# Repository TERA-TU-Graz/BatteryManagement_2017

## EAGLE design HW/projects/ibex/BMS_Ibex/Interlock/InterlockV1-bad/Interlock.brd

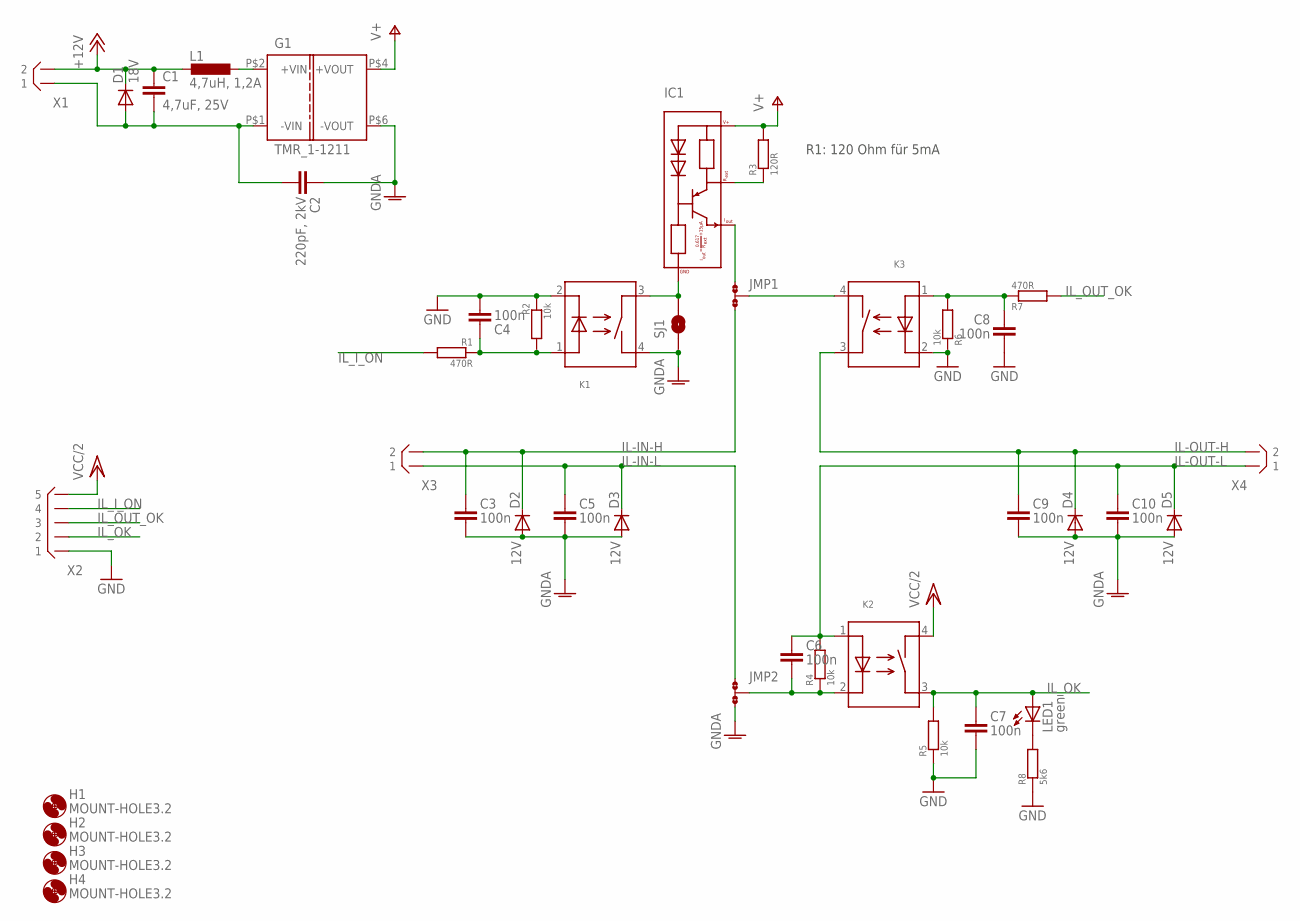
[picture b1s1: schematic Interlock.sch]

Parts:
C1: 4,7uF, 25V; C0805
C2: 220pF, 2kV; C1210_HV
C3, C4, C5, C6, C7, C8, C9, C10: 100n; C0805
D1: 18V; DO214AA
D2, D3, D4, D5: 12V; DO214AA
G1: TMR_1-1211; TMR_1-??1?
H1, H2, H3, H4: MOUNT-HOLE3.2; 3,2
IC1: PSSI2021SAY; SOT353
JMP1, JMP2: 0R-JUMPA; A0R-JMP
K1, K2, K3: ASSR-1218; SO-4
L1: 4,7uH, 1,2A; L3225M
LED1: green; CHIPLED_0805
R1, R7: 470R; R0805
R2, R4, R5, R6: 10k; R0805
R3: 120R; R0805
R8: 5k6; R0805
SJ1: SOLDERJUMPERNO; SJ_2S-NO
X1, X3, X4: B2B-XH
X2: B5B-XH

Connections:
+12V: C1.1, D1.C, L1.2, X1.P$2 (2)
GND: C4.1, C7.1, C8.1, K1.2 (I-), K3.2 (I-), R2.1, R5.1, R6.1, R8.1, X2.P$1 (1)
GNDA: C2.P$2 (2), C3.1, C5.1, C9.1, C10.1, D2.A, D3.A, D4.A, D5.A, G1.P$6 (-VOUT), JMP2.1, K1.4 (O1), SJ1.1
IL-IN-H: C3.2, D2.C, JMP1.3, X3.P$2 (2)
IL-IN-L: C5.2, D3.C, JMP2.3, X3.P$1 (1)
IL-OUT-H: C9.2, D4.C, K3.3 (O2), X4.P$2 (2)
IL-OUT-L: C6.2, C10.2, D5.C, K2.1 (I+), R4.2, X4.P$1 (1)
IL_I_ON: R1.2, X2.P$4 (4)
IL_OK: C7.2, K2.3 (O2), LED1.A, R5.2, X2.P$2 (2)
IL_OUT_OK: R7.2, X2.P$3 (3)
unnamed: IC1.4 (REXT), R3.1
unnamed: G1.P$2 (+VIN), L1.1
unnamed: C8.2, K3.1 (I+), R6.2, R7.1
unnamed: JMP1.2, K3.4 (O1)
unnamed: C1.2, C2.P$1 (1), D1.A, G1.P$1 (-VIN), X1.P$1 (1)
unnamed: IC1.2 (IOUT), JMP1.1
unnamed: C6.1, JMP2.2, K2.2 (I-), R4.1
unnamed: IC1.3 (GND), K1.3 (O2), SJ1.2
unnamed: C4.2, K1.1 (I+), R1.1, R2.2
unnamed: LED1.C, R8.2
V+: G1.P$4 (+VOUT), IC1.5 (VSS), R3.2
VCC/2: K2.4 (O1), X2.P$5 (5)

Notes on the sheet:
R1: 120 Ohm für 5mA

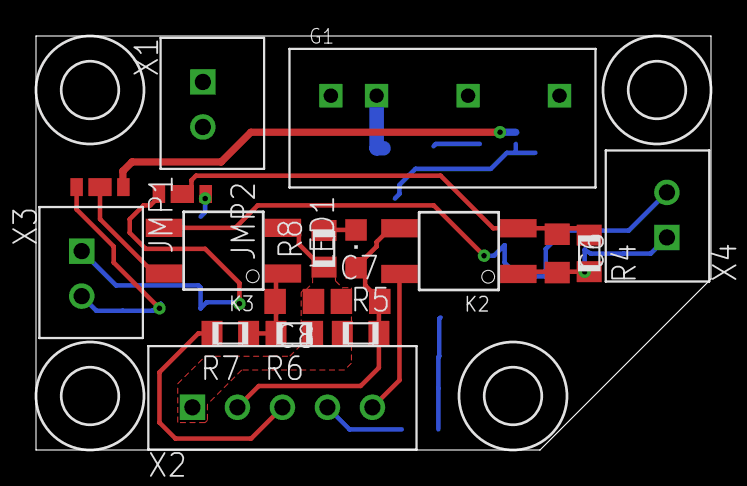
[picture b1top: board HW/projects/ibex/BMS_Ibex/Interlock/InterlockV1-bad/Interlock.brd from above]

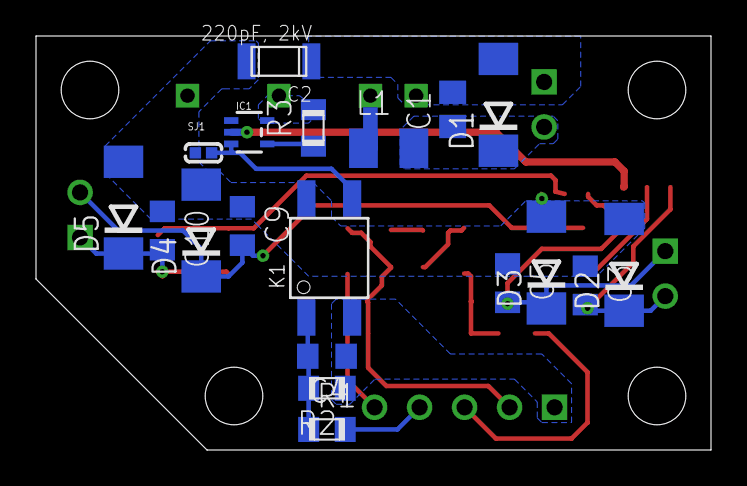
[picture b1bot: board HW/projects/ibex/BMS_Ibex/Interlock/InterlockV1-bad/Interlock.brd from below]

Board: 4 copper layers, 37.5 x 23.0 mm, 41 parts (19 on the bottom side), 22 nets.

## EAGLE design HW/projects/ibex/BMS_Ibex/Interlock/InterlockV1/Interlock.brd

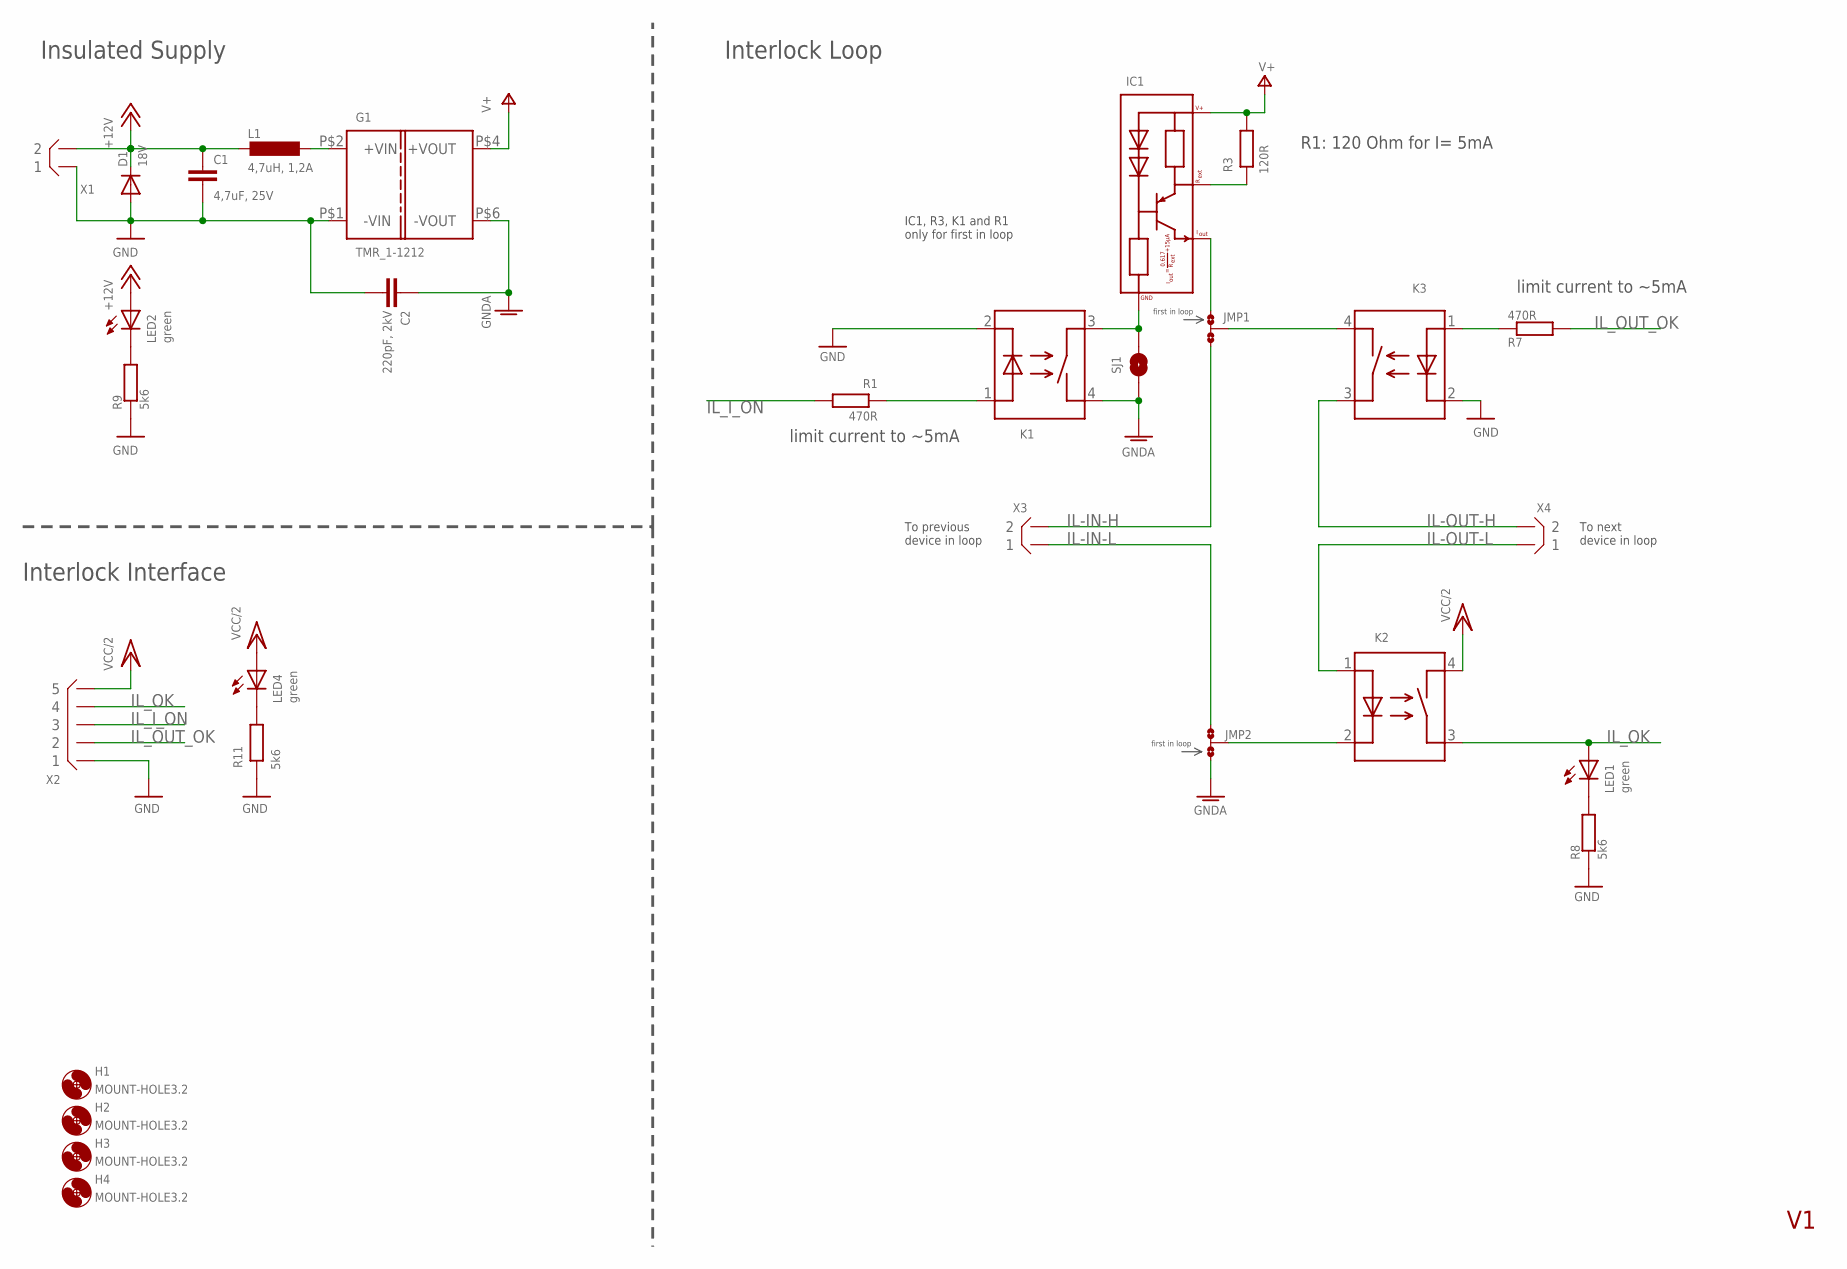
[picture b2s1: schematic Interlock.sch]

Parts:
C1: 4,7uF, 25V; C0805
C2: 220pF, 2kV; C1210_HV
D1: 18V; DO214AA
G1: TMR_1-1212; TMR_1-??1?
H1, H2, H3, H4: MOUNT-HOLE3.2; 3,2
IC1: PSSI2021SAY; SOT353
JMP1, JMP2: 0R-JUMPA; A0R-JMP
K1, K2, K3: ASSR-1218; SO-4
L1: 4,7uH, 1,2A; L3225M
LED1, LED2, LED4: green; CHIPLED_0805
R1, R7: 470R; R0805
R3: 120R; R0805
R8, R9, R11: 5k6; R0805
SJ1: SOLDERJUMPERNO; SJ_2S-NO
X1, X3, X4: B2B-XH
X2: B5B-XH

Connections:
+12V: C1.1, D1.C, L1.2, LED2.A, X1.P$2 (2)
GND: C1.2, C2.P$1 (1), D1.A, G1.P$1 (-VIN), K1.2 (I-), K3.2 (I-), R8.1, R9.1, R11.1, X1.P$1 (1), X2.P$1 (1)
GNDA: C2.P$2 (2), G1.P$6 (-VOUT), JMP2.1, K1.4 (O1), SJ1.1
IL-IN-H: JMP1.3, X3.P$2 (2)
IL-IN-L: JMP2.3, X3.P$1 (1)
IL-OUT-H: K3.3 (O2), X4.P$2 (2)
IL-OUT-L: K2.1 (I+), X4.P$1 (1)
IL_I_ON: R1.2, X2.P$3 (3)
IL_OK: K2.3 (O2), LED1.A, X2.P$4 (4)
IL_OUT_OK: R7.2, X2.P$2 (2)
unnamed: IC1.4 (REXT), R3.1
unnamed: G1.P$2 (+VIN), L1.1
unnamed: K3.1 (I+), R7.1
unnamed: JMP1.2, K3.4 (O1)
unnamed: IC1.2 (IOUT), JMP1.1
unnamed: JMP2.2, K2.2 (I-)
unnamed: IC1.3 (GND), K1.3 (O2), SJ1.2
unnamed: LED2.C, R9.2
unnamed: K1.1 (I+), R1.1
unnamed: LED4.C, R11.2
unnamed: LED1.C, R8.2
V+: G1.P$4 (+VOUT), IC1.5 (VSS), R3.2
VCC/2: K2.4 (O1), LED4.A, X2.P$5 (5)

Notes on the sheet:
R1: 120 Ohm for I= 5mA
limit current to ~5mA
Insulated Supply
Interlock Loop
Interlock Interface
IC1, R3, K1 and R1 only for first in loop
first in loop
To previous device in loop
To next device in loop

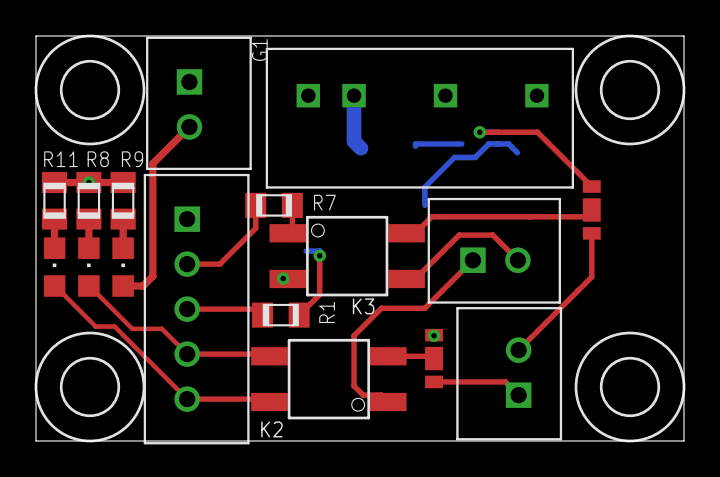
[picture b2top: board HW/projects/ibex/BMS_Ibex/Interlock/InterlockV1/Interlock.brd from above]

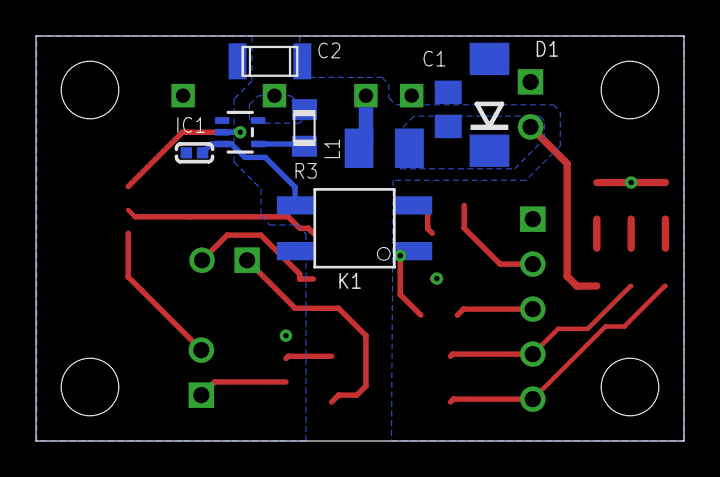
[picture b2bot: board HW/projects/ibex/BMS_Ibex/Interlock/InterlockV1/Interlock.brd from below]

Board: 4 copper layers, 36.0 x 22.5 mm, 29 parts (8 on the bottom side), 23 nets.

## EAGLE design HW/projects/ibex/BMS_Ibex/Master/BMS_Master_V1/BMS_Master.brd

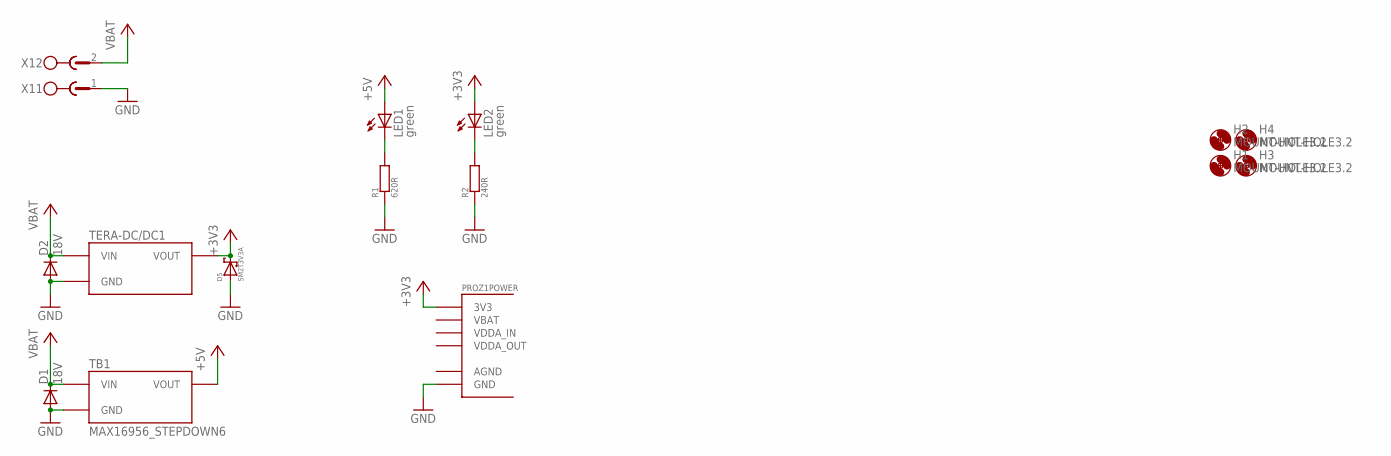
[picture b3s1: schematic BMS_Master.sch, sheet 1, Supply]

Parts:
D1, D2: 18V; DO214AA
D5: SM2T3V3A
H1, H2, H3, H4: MOUNT-HOLE3.2; 3,2
LED1, LED2: green; CHIP-LED0805
PROZ1: STM32F4_PROZESSORBOARDRPZ; STM32F4_PROZESSORBOARD
R1: 620R; R0805
R2: 240R; R0805
TB1: MAX16956_STEPDOWN6
TERA-DC/DC1: MAX5035_STEPDOWN3
X1: MSTBX2MSTBV2_GF; MSTBV2_GF

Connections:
+3V3: D5.P$2, LED2.A, PROZ1.45 (3V3), PROZ1.46 (3V3), TERA-DC/DC1.VOUT; also elsewhere on the board
+5V: LED1.A, TB1.VOUT; also elsewhere on the board
GND: D1.A, D2.A, D5.P$1, D5.P$11, PROZ1.47 (GND), PROZ1.48 (GND), R1.1, R2.1, TB1.GND, TB1.GND2 (GND), TERA-DC/DC1.GND@1 (GND), TERA-DC/DC1.GND@2 (GND), X1.1; also elsewhere on the board
unnamed: LED1.C, R1.2
unnamed: LED2.C, R2.2
VBAT: D1.C, D2.C, TB1.VIN, TERA-DC/DC1.VIN, X1.2; also elsewhere on the board

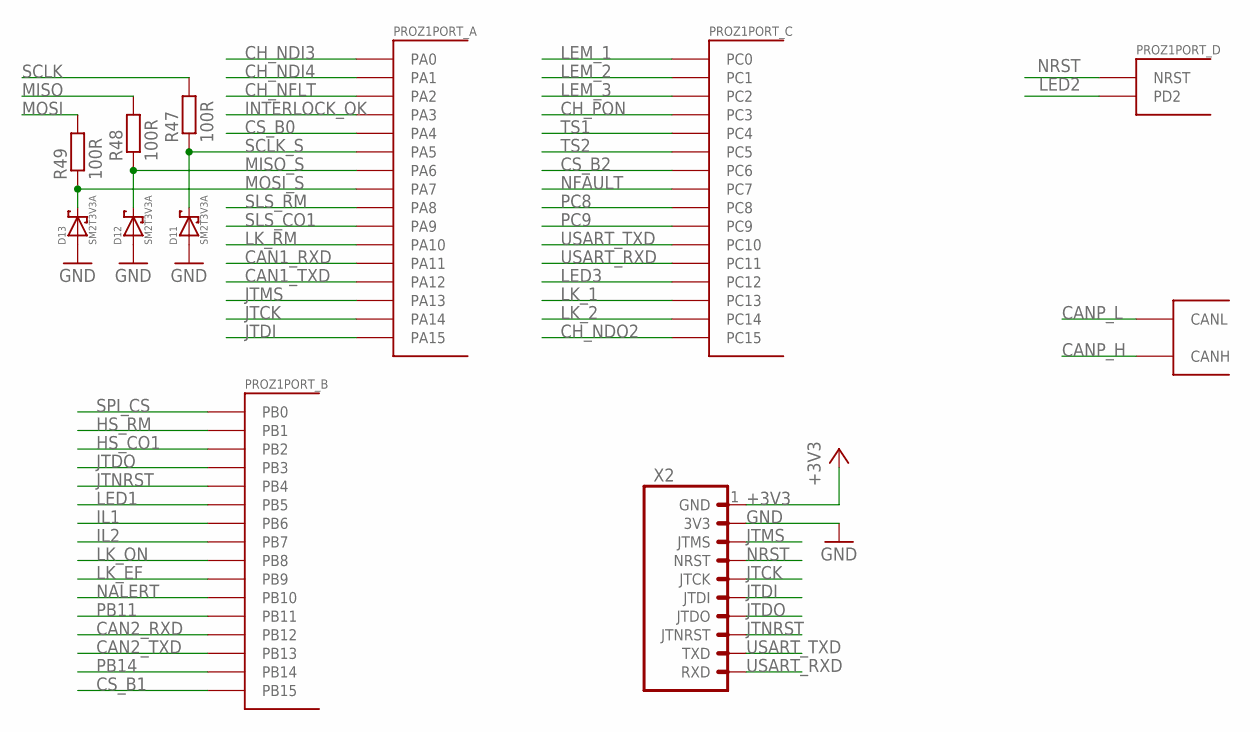
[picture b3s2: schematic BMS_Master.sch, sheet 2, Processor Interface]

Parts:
D11, D12, D13: SM2T3V3A
PROZ1: STM32F4_PROZESSORBOARDRPZ; STM32F4_PROZESSORBOARD
R47, R48, R49: 100R; R0805
X2: TERA-PROG-DEBUG-10GERADE; 90130-1110

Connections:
+3V3: X2.1 (GND); also elsewhere on the board
CAN1_RXD: PROZ1.26 (PA11); also elsewhere on the board
CAN1_TXD: PROZ1.24 (PA12); also elsewhere on the board
CAN2_RXD: PROZ1.50 (PB12); also elsewhere on the board
CAN2_TXD: PROZ1.49 (PB13); also elsewhere on the board
CANP_H: PROZ1.31 (CANH); also elsewhere on the board
CANP_L: PROZ1.32 (CANL); also elsewhere on the board
CH_NDI3: PROZ1.7 (PA0); also elsewhere on the board
CH_NDI4: PROZ1.5 (PA1); also elsewhere on the board
CH_NDO2: PROZ1.19 (PC15); also elsewhere on the board
CH_NFLT: PROZ1.3 (PA2); also elsewhere on the board
CH_PON: PROZ1.9 (PC3); also elsewhere on the board
CS_B0: PROZ1.43 (PA4); also elsewhere on the board
CS_B1: PROZ1.51 (PB15); also elsewhere on the board
CS_B2: PROZ1.52 (PC6); also elsewhere on the board
GND: D11.P$1, D11.P$11, D12.P$1, D12.P$11, D13.P$1, D13.P$11, X2.2 (3V3); also elsewhere on the board
HS_CO1: PROZ1.36 (PB2); also elsewhere on the board
HS_RM: PROZ1.37 (PB1); also elsewhere on the board
IL1: PROZ1.14 (PB6); also elsewhere on the board
IL2: PROZ1.12 (PB7); also elsewhere on the board
INTERLOCK_OK: PROZ1.44 (PA3); also elsewhere on the board
JTCK: PROZ1.18 (PA14), X2.5 (JTCK)
JTDI: PROZ1.16 (PA15), X2.6 (JTDI)
JTDO: PROZ1.20 (PB3), X2.7 (JTDO)
JTMS: PROZ1.59 (PA13), X2.3 (JTMS)
JTNRST: PROZ1.22 (PB4), X2.8 (JTNRST)
LED1: PROZ1.25 (PB5)
LED2: PROZ1.27 (PD2)
LED3: PROZ1.29 (PC12)
LEM_1: PROZ1.15 (PC0); also elsewhere on the board
LEM_2: PROZ1.13 (PC1); also elsewhere on the board
LEM_3: PROZ1.11 (PC2); also elsewhere on the board
LK_1: PROZ1.23 (PC13); also elsewhere on the board
LK_2: PROZ1.21 (PC14); also elsewhere on the board
LK_EF: PROZ1.8 (PB9); also elsewhere on the board
LK_ON: PROZ1.10 (PB8); also elsewhere on the board
LK_RM: PROZ1.58 (PA10); also elsewhere on the board
MISO: R48.2; also elsewhere on the board
MISO_S: D12.P$2, PROZ1.42 (PA6), R48.1
MOSI: R49.2; also elsewhere on the board
MOSI_S: D13.P$2, PROZ1.41 (PA7), R49.1
NALERT: PROZ1.35 (PB10); also elsewhere on the board
NFAULT: PROZ1.53 (PC7); also elsewhere on the board
NRST: PROZ1.17 (NRST), X2.4 (NRST)
PB11: PROZ1.34 (PB11)
PB14: PROZ1.33 (PB14)
PC8: PROZ1.54 (PC8)
PC9: PROZ1.55 (PC9)
SCLK: R47.2; also elsewhere on the board
SCLK_S: D11.P$2, PROZ1.60 (PA5), R47.1
SLS_CO1: PROZ1.57 (PA9); also elsewhere on the board
SLS_RM: PROZ1.56 (PA8); also elsewhere on the board
SPI_CS: PROZ1.38 (PB0); also elsewhere on the board
TS1: PROZ1.40 (PC4); also elsewhere on the board
TS2: PROZ1.39 (PC5); also elsewhere on the board
USART_RXD: PROZ1.30 (PC11), X2.10 (RXD)
USART_TXD: PROZ1.28 (PC10), X2.9 (TXD)

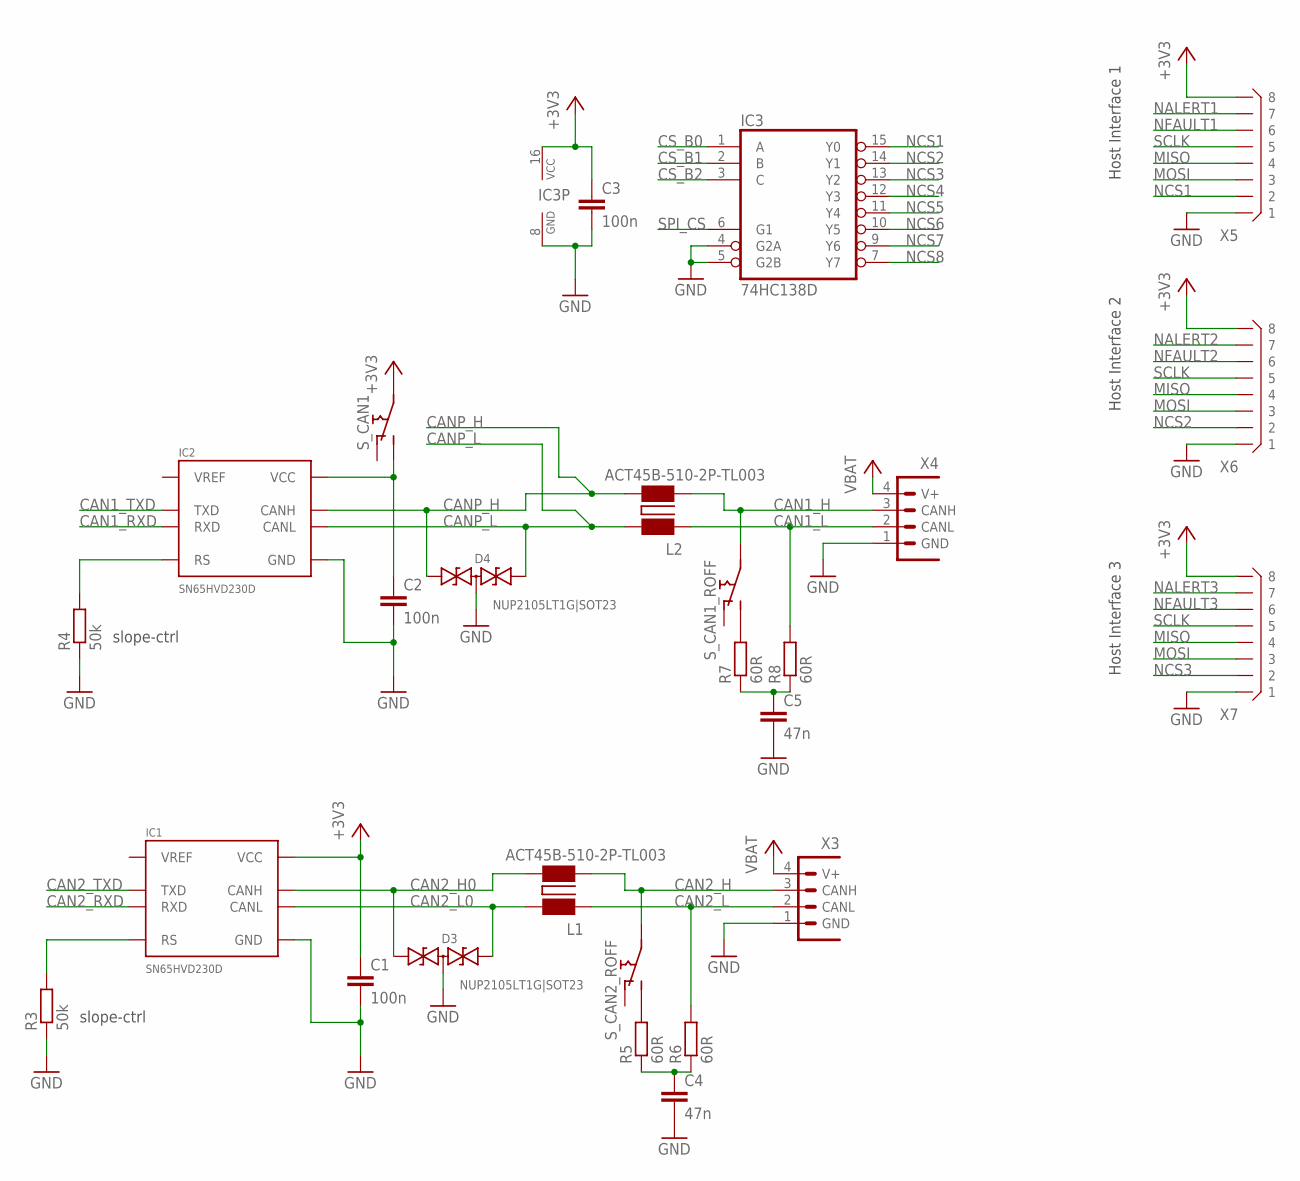
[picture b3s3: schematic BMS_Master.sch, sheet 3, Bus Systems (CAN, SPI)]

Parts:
C1, C2, C3: 100n; C0805
C4, C5: 47n; C0805
D3, D4: NUP2105LT1G|SOT23; SOT23
IC1, IC2: SN65HVD230D; SO08
IC3: 74HC138D; SO16
L1, L2: ACT45B-510-2P-TL003; ACT45B
R3, R4: 50k; R0805
R5, R6, R7, R8: 60R; R0805
S_CAN1, S_CAN1_ROFF, S_CAN2_ROFF: JUMPER_ORS; J_OR_S
X3, X4: CIOC_4-1-FV-A_CAN-BELEGUNG; CIOC_4-1-FV
X5, X6, X7: B8B-XH

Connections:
+3V3: C1.1, C3.1, IC1.3 (VCC), IC3.16 (VCC), S_CAN1.P$1, X5.P$8 (8), X6.P$8 (8), X7.P$8 (8); also elsewhere on the board
CAN1_H: L2.P$1 (1), S_CAN1_ROFF.P$1, X4.3 (CANH)
CAN1_L: L2.P$3 (3), R8.2, X4.2 (CANL)
CAN1_RXD: IC2.4 (RXD); also elsewhere on the board
CAN1_TXD: IC2.1 (TXD); also elsewhere on the board
CAN2_H: L1.P$1 (1), S_CAN2_ROFF.P$1, X3.3 (CANH)
CAN2_H0: D3.1, IC1.7 (CANH), L1.P$2 (2)
CAN2_L: L1.P$3 (3), R6.2, X3.2 (CANL)
CAN2_L0: D3.2, IC1.6 (CANL), L1.P$4 (4)
CAN2_RXD: IC1.4 (RXD); also elsewhere on the board
CAN2_TXD: IC1.1 (TXD); also elsewhere on the board
CANP_H: D4.1, IC2.7 (CANH), L2.P$2 (2); also elsewhere on the board
CANP_L: D4.2, IC2.6 (CANL), L2.P$4 (4); also elsewhere on the board
CS_B0: IC3.1 (A); also elsewhere on the board
CS_B1: IC3.2 (B); also elsewhere on the board
CS_B2: IC3.3 (C); also elsewhere on the board
GND: C1.2, C2.2, C3.2, C4.2, C5.2, D3.3, D4.3, IC1.2 (GND), IC2.2 (GND), IC3.4 (G2A), IC3.5 (G2B), IC3.8 (GND), R3.1, R4.1, X3.1 (GND), X4.1 (GND), X5.P$1 (1), X6.P$1 (1), X7.P$1 (1); also elsewhere on the board
MISO: X5.P$4 (4), X6.P$4 (4), X7.P$4 (4); also elsewhere on the board
MOSI: X5.P$3 (3), X6.P$3 (3), X7.P$3 (3); also elsewhere on the board
unnamed: C5.1, R7.1, R8.1
unnamed: C2.1, IC2.3 (VCC), S_CAN1.P$2
unnamed: IC2.8 (RS), R4.2
unnamed: C4.1, R5.1, R6.1
unnamed: R7.2, S_CAN1_ROFF.P$2
unnamed: IC1.8 (RS), R3.2
unnamed: R5.2, S_CAN2_ROFF.P$2
NALERT1: X5.P$7 (7); also elsewhere on the board
NALERT2: X6.P$7 (7); also elsewhere on the board
NALERT3: X7.P$7 (7); also elsewhere on the board
NCS1: IC3.15 (Y0), X5.P$2 (2)
NCS2: IC3.14 (Y1), X6.P$2 (2)
NCS3: IC3.13 (Y2), X7.P$2 (2)
NCS4: IC3.12 (Y3); also elsewhere on the board
NCS5: IC3.11 (Y4); also elsewhere on the board
NCS6: IC3.10 (Y5)
NCS7: IC3.9 (Y6)
NCS8: IC3.7 (Y7)
NFAULT1: X5.P$6 (6); also elsewhere on the board
NFAULT2: X6.P$6 (6); also elsewhere on the board
NFAULT3: X7.P$6 (6); also elsewhere on the board
SCLK: X5.P$5 (5), X6.P$5 (5), X7.P$5 (5); also elsewhere on the board
SPI_CS: IC3.6 (G1); also elsewhere on the board
VBAT: X3.4 (V+), X4.4 (V+); also elsewhere on the board

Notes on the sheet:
slope-ctrl
Host Interface 1
Host Interface 2
Host Interface 3

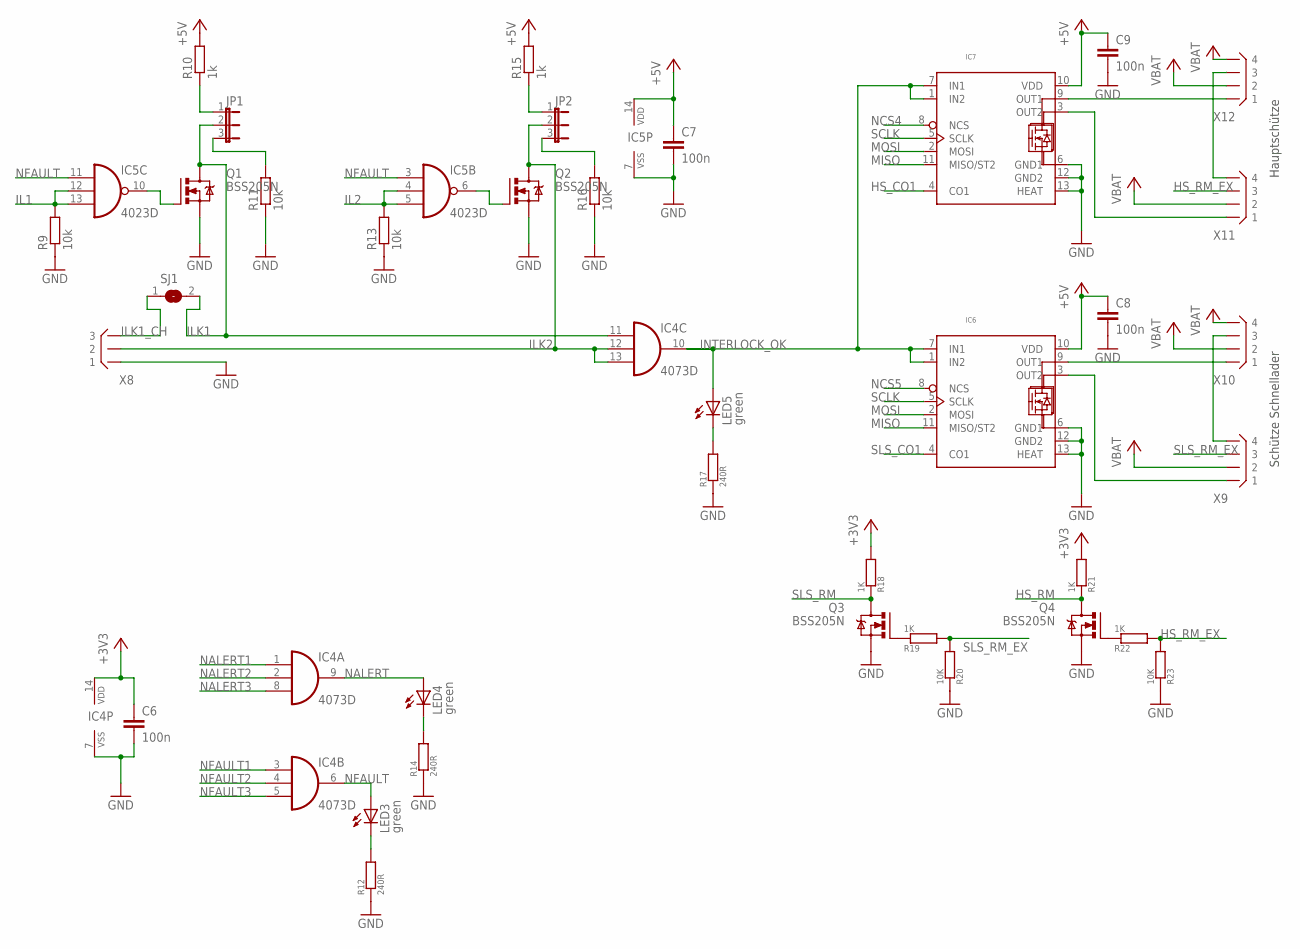
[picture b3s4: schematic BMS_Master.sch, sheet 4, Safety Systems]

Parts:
C6, C7, C8, C9: 100n; C0805
IC4: 4073D; SO14
IC5: 4023D; SO14
IC6, IC7: TLE8102SGN; INF-PG-DSO-12-11_N_1PRIMARY
JP1, JP2: JP2E; JP2
LED3, LED4, LED5: green; CHIPLED_0805
Q1, Q2, Q3, Q4: BSS205N; SOT23
R9, R11, R13, R16: 10k; R0805
R10, R15: 1k; R0805
R12, R14, R17: 240R; R0805
R18, R19, R21, R22: 1K; R0805
R20, R23: 10K; R0805
SJ1: SJ
X8: B3B-XH
X9, X10, X11, X12: B4B-XH

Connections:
+3V3: C6.1, IC4.14 (VDD), R18.2, R21.2; also elsewhere on the board
+5V: C7.1, C8.1, C9.1, IC5.14 (VDD), IC6.10 (VDD), IC7.10 (VDD), R10.2, R15.2; also elsewhere on the board
GND: C6.2, C7.2, C8.2, C9.2, IC4.7 (VSS), IC5.7 (VSS), IC6.6 (GND1), IC6.12 (GND2), IC6.13 (HEAT), IC7.6 (GND1), IC7.12 (GND2), IC7.13 (HEAT), Q1.2 (S), Q2.2 (S), Q3.2 (S), Q4.2 (S), R9.1, R11.1, R12.1, R13.1, R14.1, R16.1, R17.1, R20.1, R23.1, X8.P$1 (1); also elsewhere on the board
HS_CO1: IC7.4 (CO1); also elsewhere on the board
HS_RM: Q4.3 (D), R21.1; also elsewhere on the board
HS_RM_EX: R22.2, R23.2, X11.P$3 (3)
IL1: IC5.12 (I1), IC5.13 (I2), R9.2; also elsewhere on the board
IL2: IC5.4 (I1), IC5.5 (I2), R13.2; also elsewhere on the board
ILK1: IC4.11 (I0), JP1.2, Q1.3 (D), SJ1.2; also elsewhere on the board
ILK1_CH: SJ1.1, X8.P$3 (3); also elsewhere on the board
ILK2: IC4.12 (I1), IC4.13 (I2), JP2.2, Q2.3 (D), X8.P$2 (2)
INTERLOCK_OK: IC4.10 (O), IC6.1 (IN2), IC6.7 (IN1), IC7.1 (IN2), IC7.7 (IN1), LED5.A; also elsewhere on the board
MISO: IC6.11 (MISO/ST2), IC7.11 (MISO/ST2); also elsewhere on the board
MOSI: IC6.2 (MOSI), IC7.2 (MOSI); also elsewhere on the board
unnamed: X9.P$4 (4), X10.P$3 (3)
unnamed: IC7.3 (OUT2), X11.P$1 (1)
unnamed: IC6.9 (OUT1), X10.P$1 (1)
unnamed: X11.P$4 (4), X12.P$3 (3)
unnamed: IC6.3 (OUT2), X9.P$1 (1)
unnamed: IC7.9 (OUT1), X12.P$1 (1)
unnamed: JP1.1, R10.1
unnamed: IC5.10 (O), Q1.1 (G)
unnamed: IC5.6 (O), Q2.1 (G)
unnamed: JP2.1, R15.1
unnamed: JP2.3, R16.2
unnamed: JP1.3, R11.2
unnamed: LED5.C, R17.2
unnamed: LED4.C, R14.2
unnamed: LED3.C, R12.2
unnamed: Q3.1 (G), R19.1
unnamed: Q4.1 (G), R22.1
NALERT: IC4.9 (O), LED4.A; also elsewhere on the board
NALERT1: IC4.1 (I0); also elsewhere on the board
NALERT2: IC4.2 (I1); also elsewhere on the board
NALERT3: IC4.8 (I2); also elsewhere on the board
NCS4: IC7.8 (NCS); also elsewhere on the board
NCS5: IC6.8 (NCS); also elsewhere on the board
NFAULT: IC4.6 (O), IC5.3 (I0), IC5.11 (I0), LED3.A; also elsewhere on the board
NFAULT1: IC4.3 (I0); also elsewhere on the board
NFAULT2: IC4.4 (I1); also elsewhere on the board
NFAULT3: IC4.5 (I2); also elsewhere on the board
SCLK: IC6.5 (SCLK), IC7.5 (SCLK); also elsewhere on the board
SLS_CO1: IC6.4 (CO1); also elsewhere on the board
SLS_RM: Q3.3 (D), R18.1; also elsewhere on the board
SLS_RM_EX: R19.2, R20.2, X9.P$3 (3)
VBAT: X9.P$2 (2), X10.P$2 (2), X10.P$4 (4), X11.P$2 (2), X12.P$2 (2), X12.P$4 (4); also elsewhere on the board

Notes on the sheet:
Hauptschütze
Schütze Schnellader

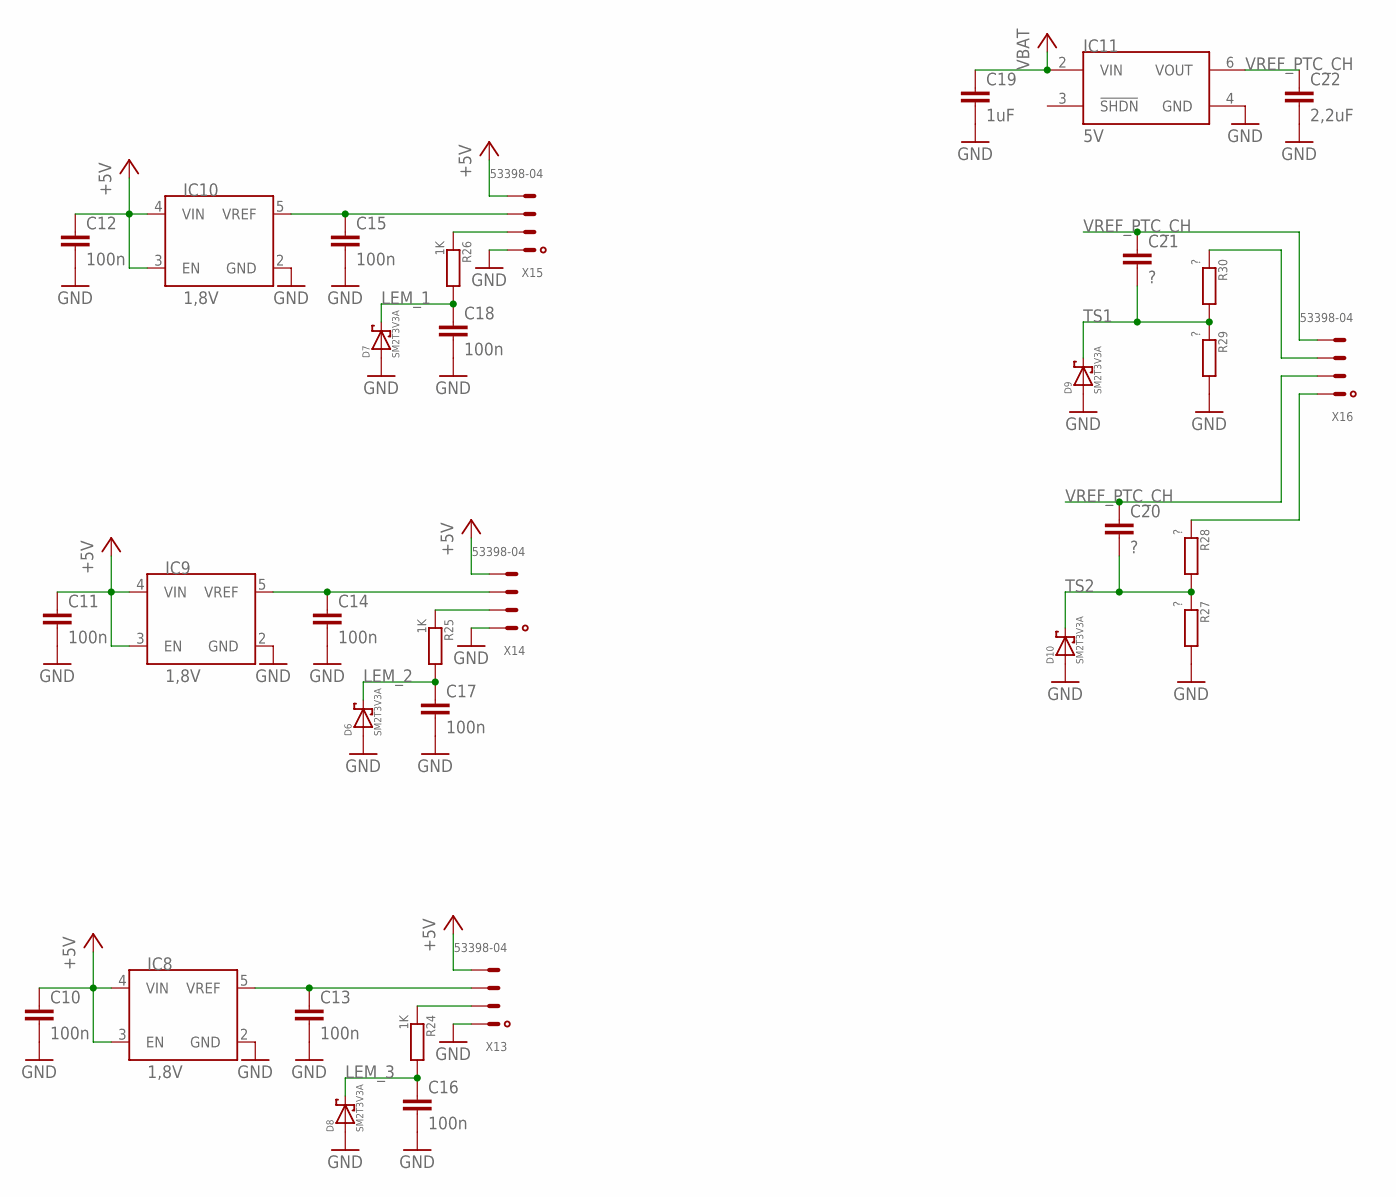
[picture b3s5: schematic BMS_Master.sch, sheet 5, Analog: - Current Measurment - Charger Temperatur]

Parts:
C10, C11, C12, C13, C14, C15, C16, C17, C18: 100n; C0805
C19: 1uF; C0805
C20, C21: ?; C0805
C22: 2,2uF; C0805
D6, D7, D8, D9, D10: SM2T3V3A
IC8, IC9, IC10: 1,8V; SOT23-5L
IC11: 5V; SO08
R24, R25, R26: 1K; R0805
R27, R28, R29, R30: ?; R0805
X13, X14, X15, X16: 53398-04

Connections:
+5V: C10.1, C11.1, C12.1, IC8.3 (EN), IC8.4 (VIN), IC9.3 (EN), IC9.4 (VIN), IC10.3 (EN), IC10.4 (VIN), X13.4, X14.4, X15.4; also elsewhere on the board
GND: C10.2, C11.2, C12.2, C13.2, C14.2, C15.2, C16.2, C17.2, C18.2, C19.2, C22.2, D6.P$1, D6.P$11, D7.P$1, D7.P$11, D8.P$1, D8.P$11, D9.P$1, D9.P$11, D10.P$1, D10.P$11, IC8.2 (GND), IC9.2 (GND), IC10.2 (GND), IC11.4 (GND), R27.2, R29.2, X13.1, X14.1, X15.1; also elsewhere on the board
LEM_1: C18.1, D7.P$2, R26.2; also elsewhere on the board
LEM_2: C17.1, D6.P$2, R25.2; also elsewhere on the board
LEM_3: C16.1, D8.P$2, R24.2; also elsewhere on the board
unnamed: C13.1, IC8.5 (VREF), X13.3
unnamed: R26.1, X15.2
unnamed: C14.1, IC9.5 (VREF), X14.3
unnamed: R30.1, X16.3
unnamed: R25.1, X14.2
unnamed: C15.1, IC10.5 (VREF), X15.3
unnamed: R24.1, X13.2
unnamed: R28.1, X16.1
TS1: C21.2, D9.P$2, R29.1, R30.2; also elsewhere on the board
TS2: C20.2, D10.P$2, R27.1, R28.2; also elsewhere on the board
VBAT: C19.1, IC11.2 (VIN); also elsewhere on the board
VREF_PTC_CH: C20.1, C21.1, C22.1, IC11.6 (VOUT), X16.2, X16.4

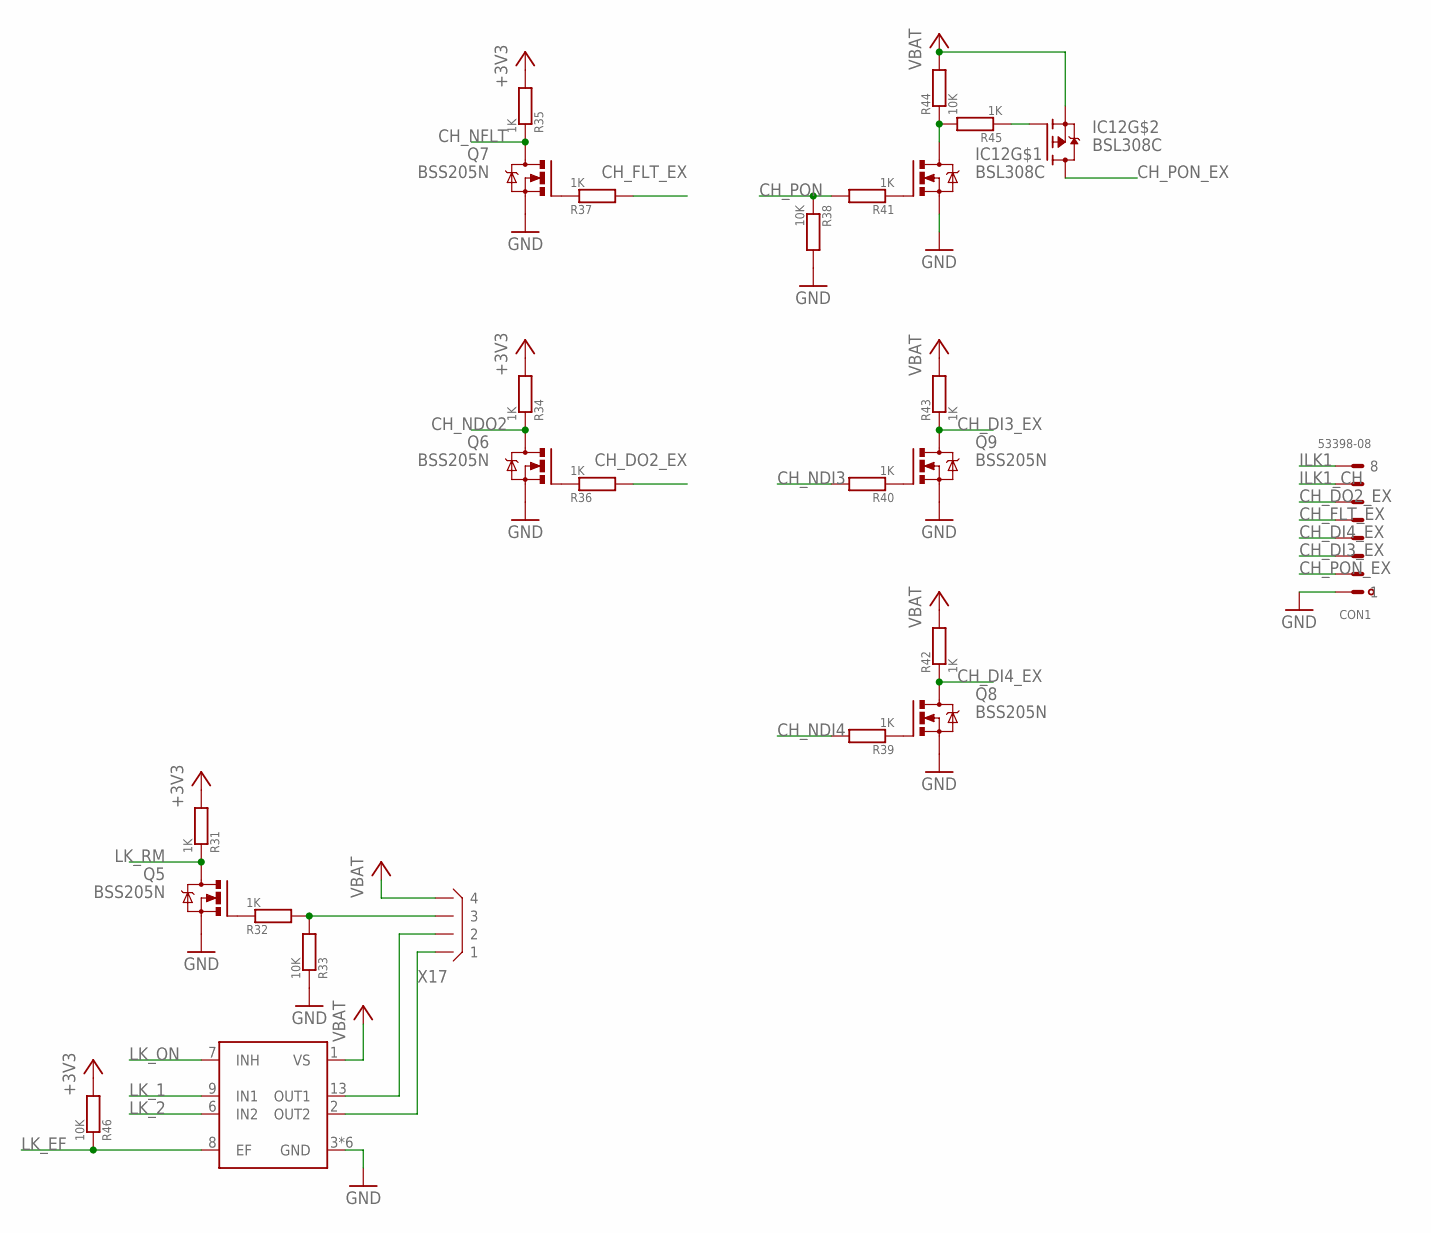
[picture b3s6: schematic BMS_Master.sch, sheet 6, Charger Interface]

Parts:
CON1: 53398-08
IC12: BSL308C; TSOP-6
IC13: TLE4207GM; INF-PG-DSO-14-22_M_1PRIMARY
Q5, Q6, Q7, Q8, Q9: BSS205N; SOT23
R31, R32, R34, R35, R36, R37, R39, R40, R41, R42, R43, R45: 1K; R0805
R33, R38, R44, R46: 10K; R0805
X17: B4B-XH

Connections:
+3V3: R31.2, R34.2, R35.2, R46.2; also elsewhere on the board
CH_DI3_EX: CON1.3, Q9.3 (D), R43.1
CH_DI4_EX: CON1.4, Q8.3 (D), R42.1
CH_DO2_EX: CON1.6, R36.2
CH_FLT_EX: CON1.5, R37.2
CH_NDI3: R40.2; also elsewhere on the board
CH_NDI4: R39.2; also elsewhere on the board
CH_NDO2: Q6.3 (D), R34.1; also elsewhere on the board
CH_NFLT: Q7.3 (D), R35.1; also elsewhere on the board
CH_PON: R38.1, R41.2; also elsewhere on the board
CH_PON_EX: CON1.2, IC12.P$4 (D)
GND: CON1.1, IC12.P$5 (S), IC13.3 (GND), IC13.4 (GND), IC13.5 (GND), IC13.10 (GND), IC13.11 (GND), IC13.12 (GND), Q5.2 (S), Q6.2 (S), Q7.2 (S), Q8.2 (S), Q9.2 (S), R33.1, R38.2; also elsewhere on the board
ILK1: CON1.8; also elsewhere on the board
ILK1_CH: CON1.7; also elsewhere on the board
LK_1: IC13.9 (IN1); also elsewhere on the board
LK_2: IC13.6 (IN2); also elsewhere on the board
LK_EF: IC13.8 (EF), R46.1; also elsewhere on the board
LK_ON: IC13.7 (INH); also elsewhere on the board
LK_RM: Q5.3 (D), R31.1; also elsewhere on the board
unnamed: Q6.1 (G), R36.1
unnamed: Q9.1 (G), R40.1
unnamed: Q5.1 (G), R32.1
unnamed: R32.2, R33.2, X17.P$3 (3)
unnamed: IC12.P$3 (G), R45.1
unnamed: IC13.13 (OUT1), X17.P$2 (2)
unnamed: IC13.2 (OUT2), X17.P$1 (1)
unnamed: IC12.P$1 (G), R41.1
unnamed: Q8.1 (G), R39.1
unnamed: Q7.1 (G), R37.1
unnamed: IC12.P$6 (D), R44.1, R45.2
VBAT: IC12.P$2 (S), IC13.1 (VS), R42.2, R43.2, R44.2, X17.P$4 (4); also elsewhere on the board

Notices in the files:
parts and their libraries:
SparkFun: Licensing: CC v3.0 Share-Alike You are welcome to use this library for commercial purposes.
